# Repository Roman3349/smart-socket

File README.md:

# Smart socket

The IQRF project to switching mains voltage.

## License
This project is licensed under the GPLv3 license:

 > Copyright (C) 2017 Roman Ondráček
 >
 > This program is free software: you can redistribute it and/or modify
 > it under the terms of the GNU General Public License as published by
 > the Free Software Foundation, either version 3 of the License, or
 > (at your option) any later version.
 > 
 > This program is distributed in the hope that it will be useful,
 > but WITHOUT ANY WARRANTY; without even the implied warranty of
 > MERCHANTABILITY or FITNESS FOR A PARTICULAR PURPOSE.  See the
 > GNU General Public License for more details.
 >
 > You should have received a copy of the GNU General Public License
 > along with this program.  If not, see <http://www.gnu.org/licenses/>.

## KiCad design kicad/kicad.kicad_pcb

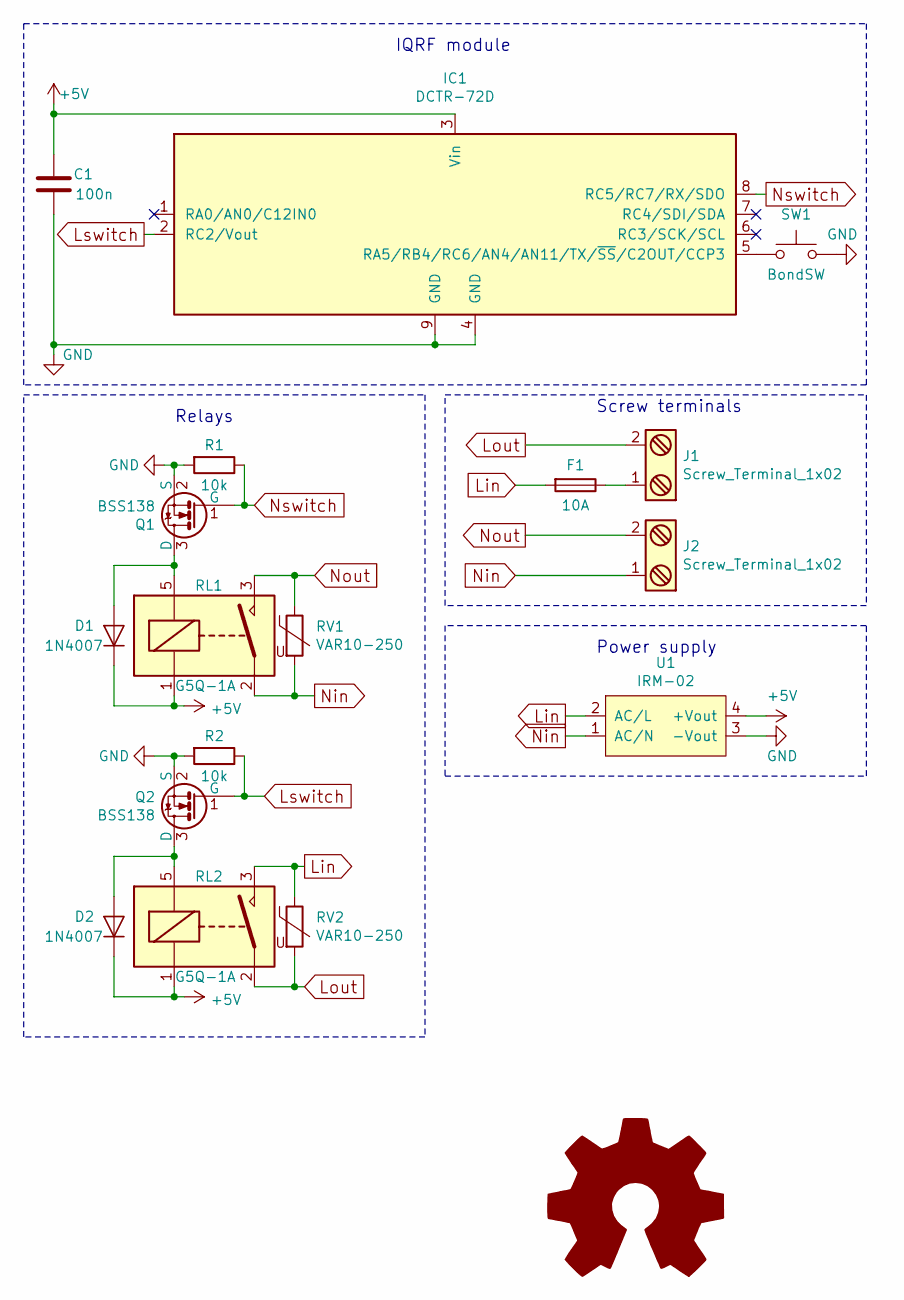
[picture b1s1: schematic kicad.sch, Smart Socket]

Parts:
C1: 100n; C_1206_HandSoldering
D1, D2: 1N4007; Diode_DO-41_SOD81_Horizontal_RM10
F1: 10A; Fuseholder5x20_horiz_open_Schurter_0031_8201
IC1: DCTR-72D; IQRF_KON-SIM-01
J1, J2: Screw_Terminal_1x02; TerminalBlock_DG300-7.5-02P_RM7.5mm_2pol
LOGO1: OPEN_HARDWARE_2; OSHW-Logo2_9.8x8mm_Copper
Q1, Q2: BSS138; SOT-23
R1, R2: 10k; R_1206_HandSoldering
RL1, RL2: G5Q-1A; Relay_SPST-NO_OMRON-G5Q
RV1, RV2: VAR10-250; RV_Disc_D12_W3.9_P7.5
SW1: BondSW; SW_PUSH_6mm
U1: IRM-02; ACDC-Converter_MeanWell-IRM-02-x

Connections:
+5V: C1.2, D1.1 (K), D2.1 (K), IC1.3 (Vin), RL1.1, RL2.1, U1.4 (+Vout)
GND: C1.1, IC1.4 (GND), IC1.9 (GND), Q1.2 (S), Q2.2 (S), R1.2, R2.2, SW1.2, U1.3 (-Vout)
Lin: F1.2, RL2.3, RV2.1, U1.2 (AC/L)
Lout: J1.2, RL2.2, RV2.2
Lswitch: IC1.2 (RC2/Vout), Q2.1 (G), R2.1
unnamed: D1.2 (A), Q1.3 (D), RL1.5
unnamed: D2.2 (A), Q2.3 (D), RL2.5
unnamed: F1.1, J1.1
unnamed: IC1.5 (RA5/RB4/RC6/AN4/AN11/TX/~SS~/C2OUT/CCP3), SW1.1
Nin: J2.1, RL1.2, RV1.2, U1.1 (AC/N)
Nout: J2.2, RL1.3, RV1.1
Nswitch: IC1.8 (RC5/RC7/RX/SDO), Q1.1 (G), R1.1

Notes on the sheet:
Relays
IQRF module
Screw terminals
Power supply

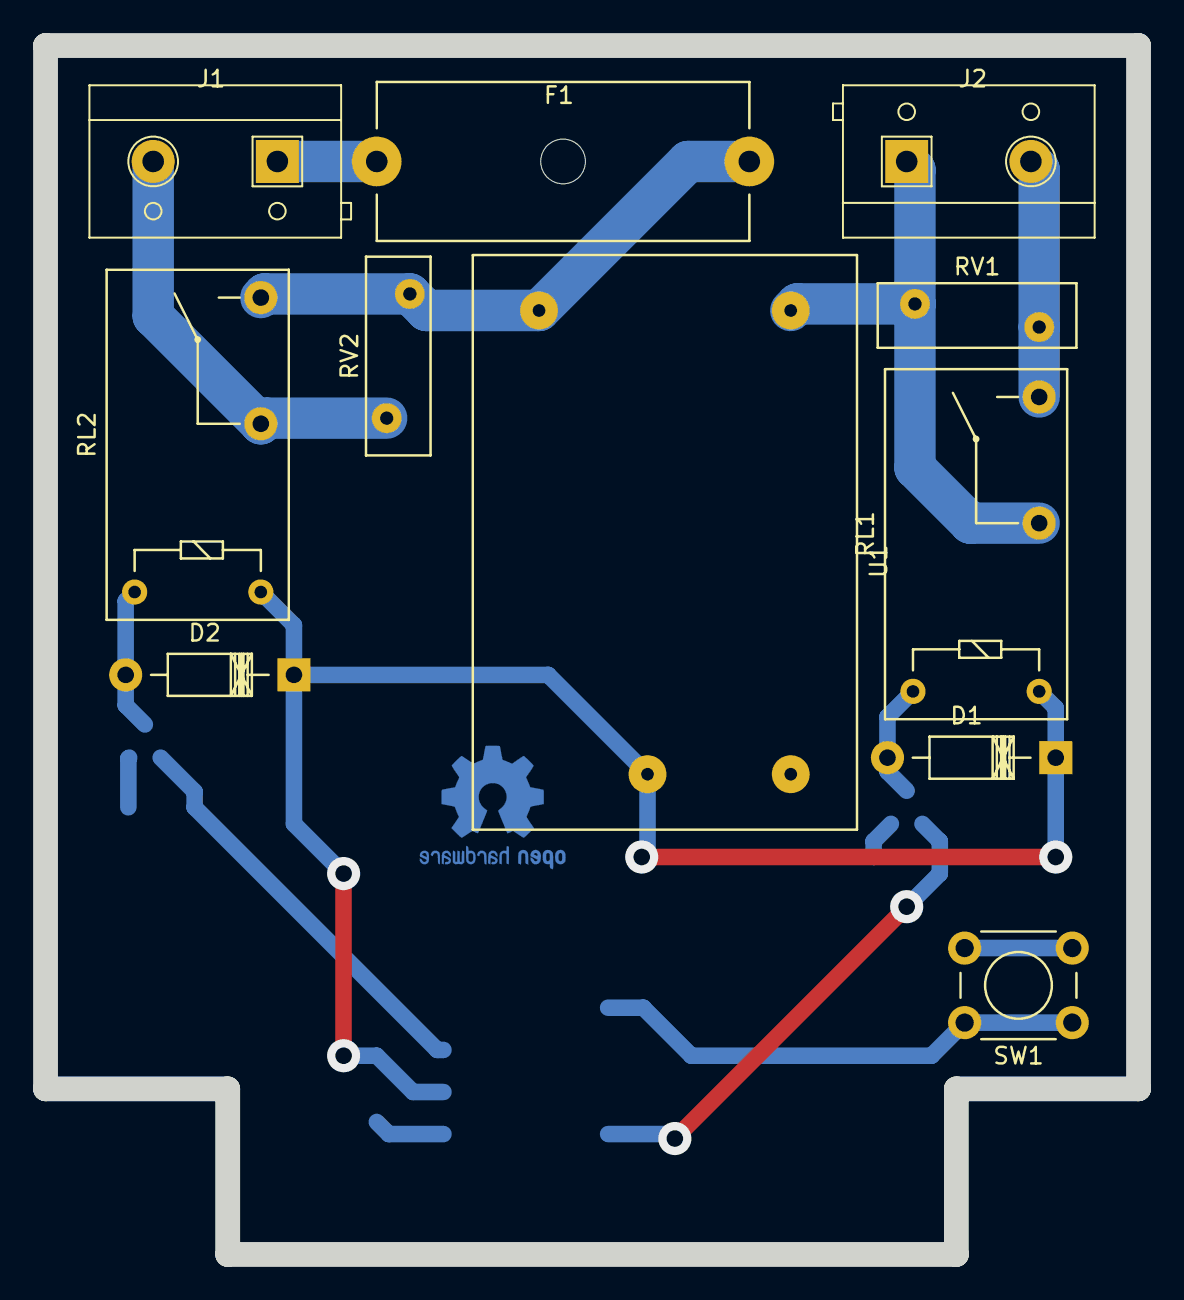
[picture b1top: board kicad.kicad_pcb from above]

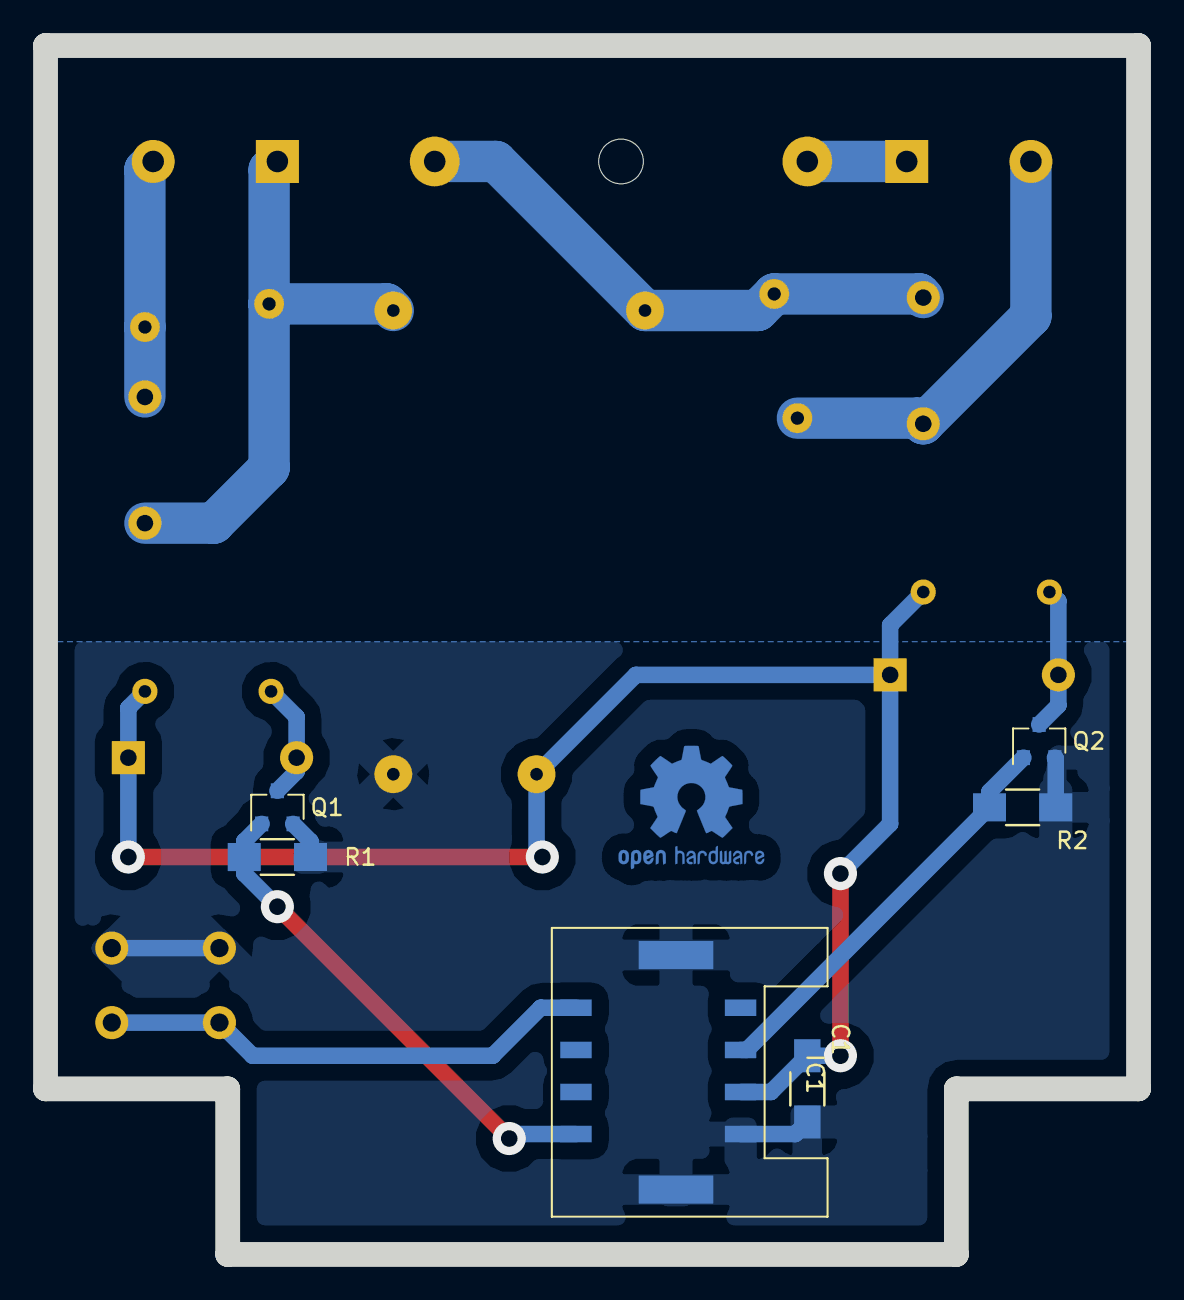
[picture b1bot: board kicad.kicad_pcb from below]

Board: 2 copper layers, 66.0 x 73.0 mm, 18 parts (7 on the bottom side), 12 nets.

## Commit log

2016-12-23 Add GPL v3 license
2016-12-24 Add skeleton of docs
2016-12-25 Update docs
2016-12-26 Add a schema of prototype
2017-01-06 Add PCB
2017-01-08 Update schematic
2017-01-18 Add IQRF Custom DPA handler
2017-01-25 Add Makefile for generating PDF file from LaTeX files
2017-01-25 Add Read me
2017-01-30 Rename the directory with documentation
2017-01-31 Fix typo in a documentation
2017-01-31 Fix encoding of file with DPA Custom handler
2017-02-01 Fix grammar on Annotation
2017-02-01 Use spaces insted of tabs
2017-02-03 Update configuration of software for gateway
2017-02-03 Move a directory with images to the directory documentation
2017-02-03 Update schematic of communication
2017-02-03 Add presentation
2017-02-10 Fix typo in documentation
2017-02-14 Fix typo in presentation
2017-03-23 Update presentation
2017-05-07 Fix typo in the czech presentation
2017-05-10 Add more information to the czech presentation
2017-05-15 Update schematic of Smart socket

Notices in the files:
kicad/kicad.sch:
License: GNU GPL v3
